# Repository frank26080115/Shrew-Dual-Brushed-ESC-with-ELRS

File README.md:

# Shrew: Dual Brushed ESC with ELRS

Shrew is family of ESCs (Electronic Speed Controller) that can drive two brushed motors, with an ELRS receiver integrated. It is designed to be as small as possible yet still pack plenty of power. It is meant for insect class combat robots.

There are three variations of Shrew

 * Shrew-Pro, for dual brushed motors up to 21A
 * Shrew-Lite, for dual brushed motors up to 3.7A
 * Shrew-Zero, not a ESC, just a receiver

All of these function as ELRS receivers with 4 or more GPIO pins, capable of controlling other ESCs or servos. These pins can output PWM, as well as better protocols such as Dshot. If you have the skills, you can even use them for I2C and such.

The input voltage ratings of Shrew is incredibly high, even Shrew-Lite can handle up to 36V, that means connecting directly to a 8S battery is not a problem (please see individual detailed specifications).

If you are using AM32 brushless ESCs with Shrew, Shrew features a webpage interface to configure the AM32 ESC. If you have 4 ESCs connected to Shrew, you can change settings on each one individually and test it immediately, all without disconnecting any wires. Plus, you can test the ESCs immediately after making a settings change through the same webpage interface.

## Design Ethos

Safety and reliability is on the top of my priority list

 * Digital protocols are safer than PWM ([why this is better](docs/Digital-Protocols-for-ESC-Control.md))
 * No-pulse failsafe mode by default ([why this is better](docs/No-Pulse-Failsafe-Mode.md))
 * No entering any unexpected modes, there is no way to accidentally enter some sort of calibration mode or binding mode
 * No dead-zone implemented, so there's no control lag at all, and there is also no need for calibration
 * Binding is done with a binding-phrase, extremely good for spare parts management of a competitive robot
 * Power input solder points are intentionally placed farther apart to prevent accidental short circuiting
 * RGB LED on it is indicative of control inputs, not just connection state
 * Top quality TCXO and a ceramic antenna for a balance between high RF performance and durability.

## User Manuals

 * [Shrew-Pro User Manual](Shrew-Pro-User-Manual.md)
 * [Shrew-Lite User Manual](Shrew-Lite-User-Manual.md)
 * [Shrew-Zero User Manual](Shrew-Zero-User-Manual.md)

## Open Source Notes

All of the circuitry is designed using CadSoft EAGLE v7. This is NOT Autodesk EAGLE, but Autodesk EAGLE can open the files.

All the manufacturing data is tailored for JLCPCB's PCBA service.

The firmware in this repo are in binary form only, but the source code for them are on a branch of a fork of ExpressLRS: https://github.com/frank26080115/ExpressLRS/tree/shrew

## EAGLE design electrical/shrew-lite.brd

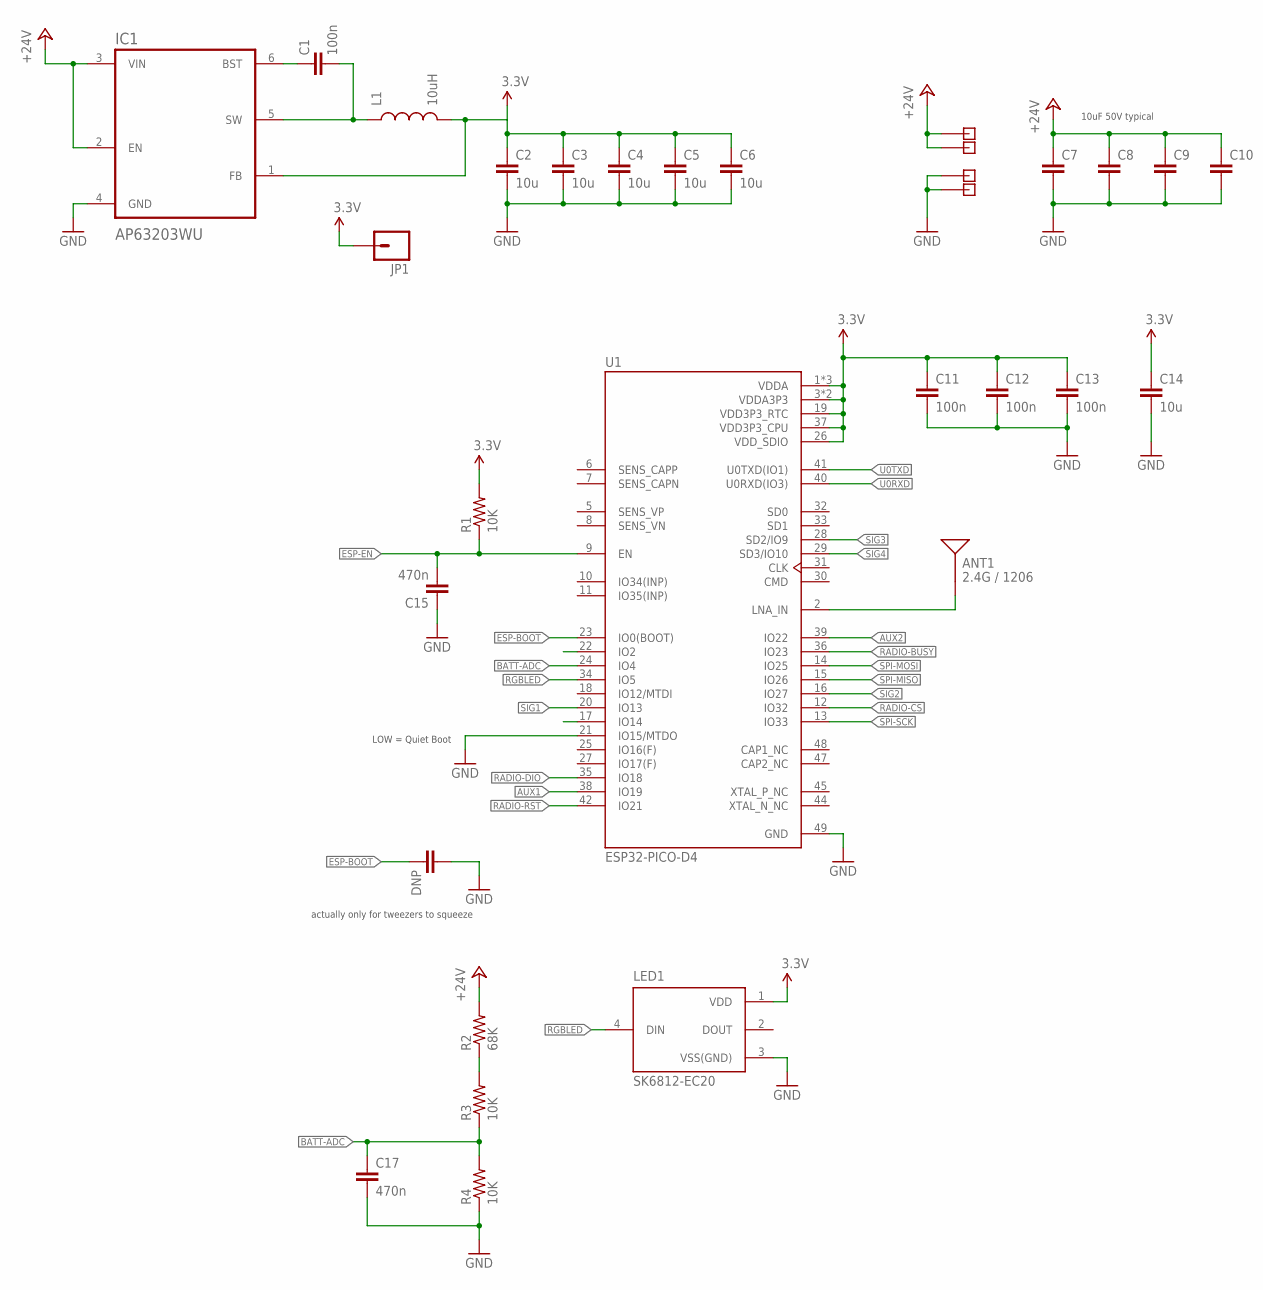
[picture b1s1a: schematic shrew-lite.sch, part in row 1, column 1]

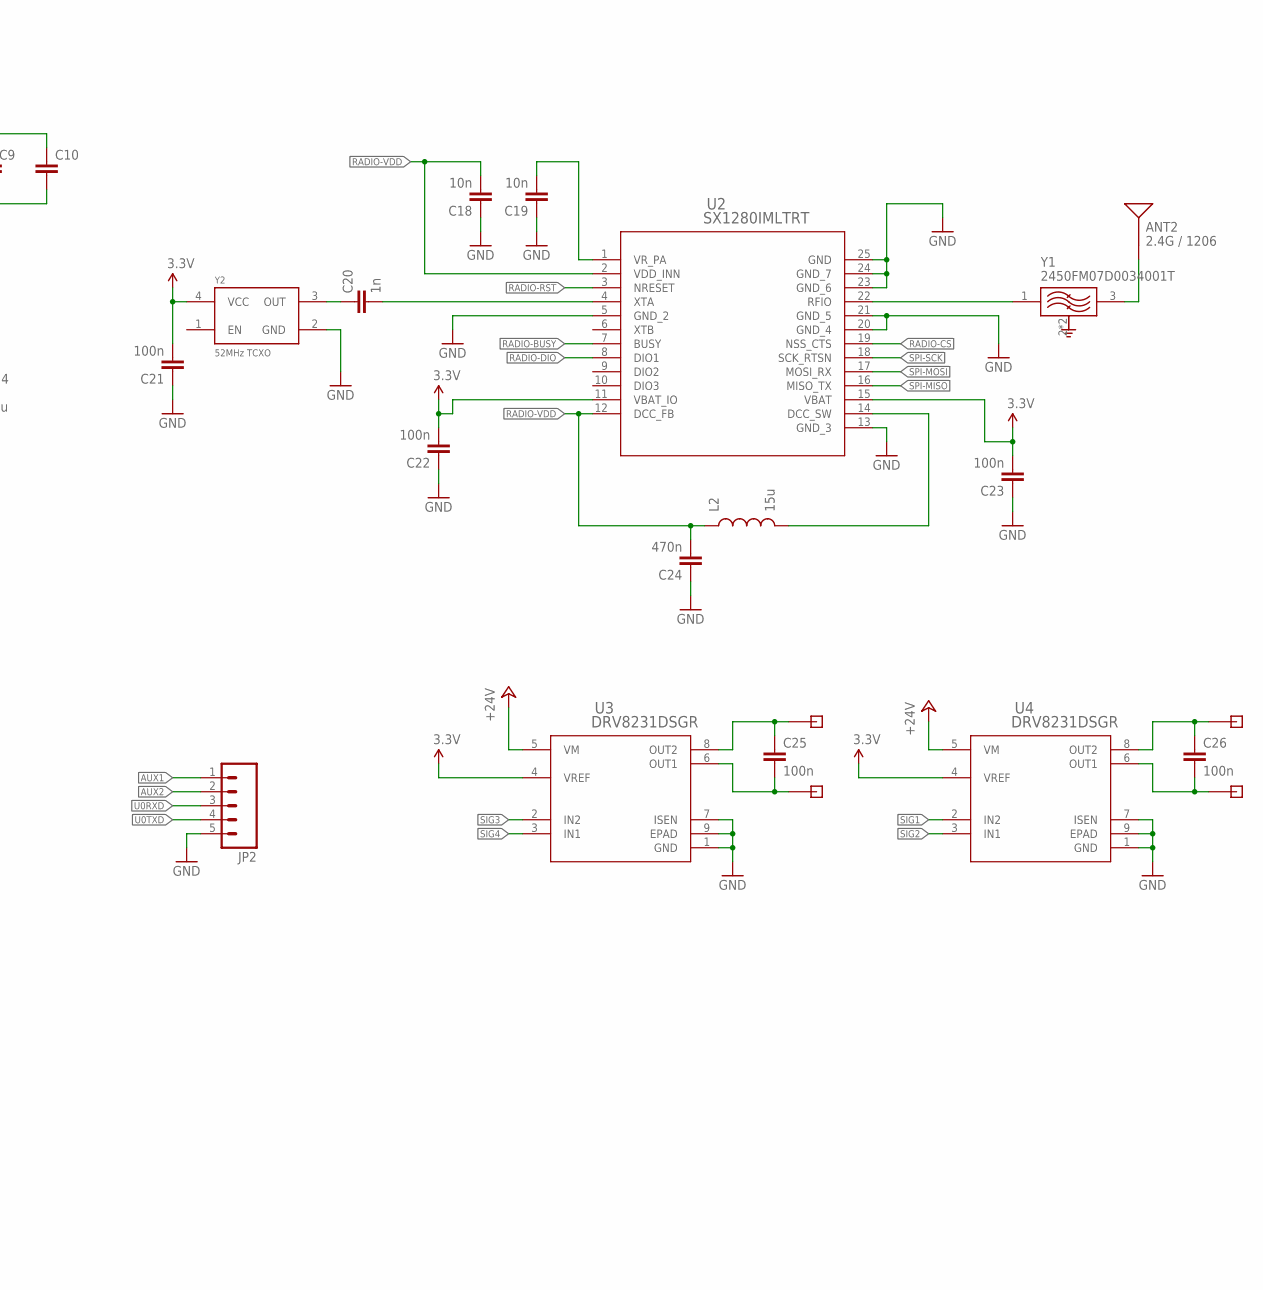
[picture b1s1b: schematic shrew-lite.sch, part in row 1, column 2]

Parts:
ANT1: 2.4G / 1206; ANTENNA-CHIP2; JLC_ROTATION 180
ANT2: 2.4G / 1206; ANTENNA-CHIP2; LCSC C127620
C1, C11, C12, C13, C21, C22, C23: 100n; 0402-REV; LCSC C1581
C2, C3, C4, C5, C6, C14: 10u; 0402-REV; LCSC C15525
C7, C8, C9, C10: 10u; 0805
C15: 470n; 0402-REV; LCSC C7393859
C16: DNP; 0402-CAP
C17, C24: 470n; 0402-REV
C18, C19: 10n; 0402-REV; LCSC C15195
C20: 1n; 0402-REV; LCSC C1523
C25, C26: 100n; 0402-CAP; LCSC C1581
IC1: AP63203WU; SOT95P280X110-6N; JLC_ROTATION 180
JP1: M01-1.0MM-TP; 1X01-1.0MM-TP
JP2: M05PTH; 1X05
L1: 10uH; 0805
L2: 15u; 0805; LCSC C6364731
LED1: SK6812-EC20
R1, R3, R4: 10K; 0402-REV; LCSC C25744
R2: 68K; 0402-REV; LCSC C2909379
U1: ESP32-PICO-D4; PQFN50P700X700X104-49N; JLC_ROTATION -90
U2: SX1280IMLTRT; QFN24_4X4_SEM; JLC_ROTATION -90
U3, U4: DRV8231DSGR; WSON8_DRV8231_TEX; JLC_ROTATION 90
X1, X2, X3, X4: PIN-1X-MED; PAD-1X-MED
X5, X6, X7, X8: PIN-1X-BIG; PAD-1X-BIG
Y1: 2450FM07D0034001T; FIL_2450FM07D0034T; LCSC C6054595
Y2: 52MHz TCXO; OSC_TG2016SMN_50.0000M-ECGNNMB; JLC_ROTATION -90

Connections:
3.3V: C2.1, C3.1, C4.1, C5.1, C6.1, C11.1, C12.1, C13.1, C14.1, C21.2, C22.2, C23.2, IC1.1 (FB), JP1.1, L1.2, LED1.1 (VDD), R1.2, U1.1 (VDDA), U1.3 (VDDA3P3), U1.4 (VDDA3P3), U1.19 (VDD3P3_RTC), U1.26 (VDD_SDIO), U1.37 (VDD3P3_CPU), U1.43 (VDDA), U1.46 (VDDA), U2.11 (VBAT_IO), U2.15 (VBAT), U3.4 (VREF), U4.4 (VREF), Y2.4 (VCC)
+24V: C7.1, C8.1, C9.1, C10.1, IC1.2 (EN), IC1.3 (VIN), R2.2, U3.5 (VM), U4.5 (VM), X1.1, X2.1
AUX1: JP2.1, U1.38 (IO19)
AUX2: JP2.2, U1.39 (IO22)
BATT-ADC: C17.1, R3.1, R4.2, U1.24 (IO4)
ESP-BOOT: C16.2, U1.23 (IO0(BOOT))
ESP-EN: C15.2, R1.1, U1.9 (EN)
GND: C2.2, C3.2, C4.2, C5.2, C6.2, C7.2, C8.2, C9.2, C10.2, C11.2, C12.2, C13.2, C14.2, C15.1, C16.1, C17.2, C18.1, C19.1, C21.1, C22.1, C23.1, C24.1, IC1.4 (GND), JP2.5, LED1.3 (VSS(GND)), R4.1, U1.21 (IO15/MTDO), U1.49 (GND), U2.5 (GND_2), U2.13 (GND_3), U2.20 (GND_4), U2.21 (GND_5), U2.23 (GND_6), U2.24 (GND_7), U2.25 (GND), U3.1 (GND), U3.7 (ISEN), U3.9 (EPAD), U4.1 (GND), U4.7 (ISEN), U4.9 (EPAD), X3.1, X4.1, Y1.2 (GND), Y1.4 (GND), Y2.2 (GND)
MOTOR1: C26.2, U4.6 (OUT1), X8.1
MOTOR2: C26.1, U4.8 (OUT2), X6.1
MOTOR3: C25.2, U3.6 (OUT1), X7.1
MOTOR4: C25.1, U3.8 (OUT2), X5.1
unnamed: ANT1.FEED, U1.2 (LNA_IN)
unnamed: C20.1, Y2.3 (OUT)
unnamed: C20.2, U2.4 (XTA)
unnamed: R2.1, R3.2
unnamed: U2.22 (RFIO), Y1.1 (IN)
unnamed: ANT2.FEED, Y1.3 (OUT)
unnamed: L2.2, U2.14 (DCC_SW)
unnamed: C1.2, IC1.5 (SW), L1.1
unnamed: C19.2, U2.1 (VR_PA)
unnamed: C1.1, IC1.6 (BST)
RADIO-BUSY: U1.36 (IO23), U2.7 (BUSY)
RADIO-CS: U1.12 (IO32), U2.19 (NSS_CTS)
RADIO-DIO: U1.35 (IO18), U2.8 (DIO1)
RADIO-RST: U1.42 (IO21), U2.3 (NRESET)
RADIO-VDD: C18.2, C24.2, L2.1, U2.2 (VDD_INN), U2.12 (DCC_FB)
RGBLED: LED1.4 (DIN), U1.34 (IO5)
SIG1: U1.20 (IO13), U4.2 (IN2)
SIG2: U1.16 (IO27), U4.3 (IN1)
SIG3: U1.28 (SD2/IO9), U3.2 (IN2)
SIG4: U1.29 (SD3/IO10), U3.3 (IN1)
SPI-MISO: U1.15 (IO26), U2.16 (MISO_TX)
SPI-MOSI: U1.14 (IO25), U2.17 (MOSI_RX)
SPI-SCK: U1.13 (IO33), U2.18 (SCK_RTSN)
U0RXD: JP2.3, U1.40 (U0RXD(IO3))
U0TXD: JP2.4, U1.41 (U0TXD(IO1))

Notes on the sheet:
actually only for tweezers to squeeze
LOW = Quiet Boot
10uF 50V typical

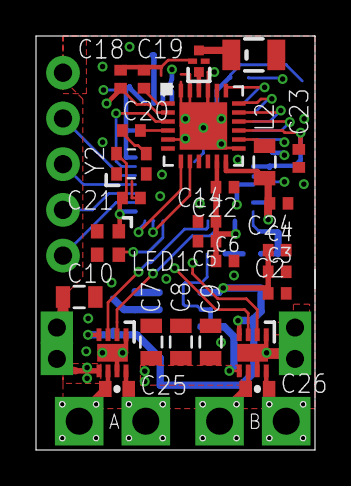
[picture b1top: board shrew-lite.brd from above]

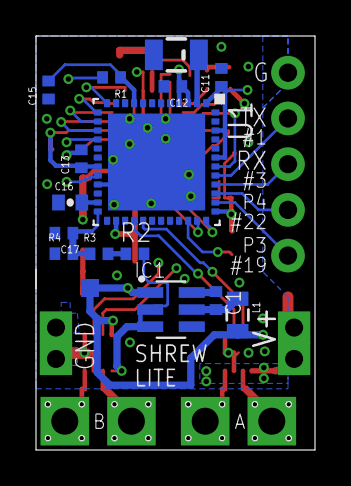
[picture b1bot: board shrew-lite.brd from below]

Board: 4 copper layers, 15.5 x 23.0 mm, 52 parts (16 on the bottom side), 37 nets.

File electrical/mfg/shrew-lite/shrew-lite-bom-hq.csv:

Comment,Designator,Footprint,LCSC Part #
0.5pF,C30,0402-REV,C258483
1n,C20,0402-REV,C307441
10K,R1 R3 R4,0402-REV,
10n,C18 C19,0402-REV,C3855387
10u,C2 C3 C4 C5 C6 C14,0402-REV,C15525
10u,C7 C8 C9 C10,0805,C2932476
10uH,L1,0805,C139245
15u,L2,0805,C486333
52MHz TCXO,Y2,OSC_TG2016SMN_50.0000M-ECGNNMB,C7503930
68K,R2,0402-REV,
100n,C1 C11 C12 C13 C21 C22 C23 C27 C28 C29 C25 C26,0402-REV,C527001
470n,C15 C17 C24,0402-REV,C106250
2450FM07D0034T,Y1,FIL_2450FM07D0034T,C2651081
ANT3216LL00R2400A,ANT1 ANT2,ANTENNA-CHIP2,C293767
AP63203WU,IC1,SOT95P280X110-6N,C780769
DRV8231DSGR,U3 U4,WSON8_DRV8231_TEX,C5139865
ESP32-PICO-D4,U1,PQFN50P700X700X104-49N,C193707
SK6812-EC20,LED1,SK6812-EC20,C2909058
SX1280IMLTRT,U2,QFN24_4X4_SEM,C125969

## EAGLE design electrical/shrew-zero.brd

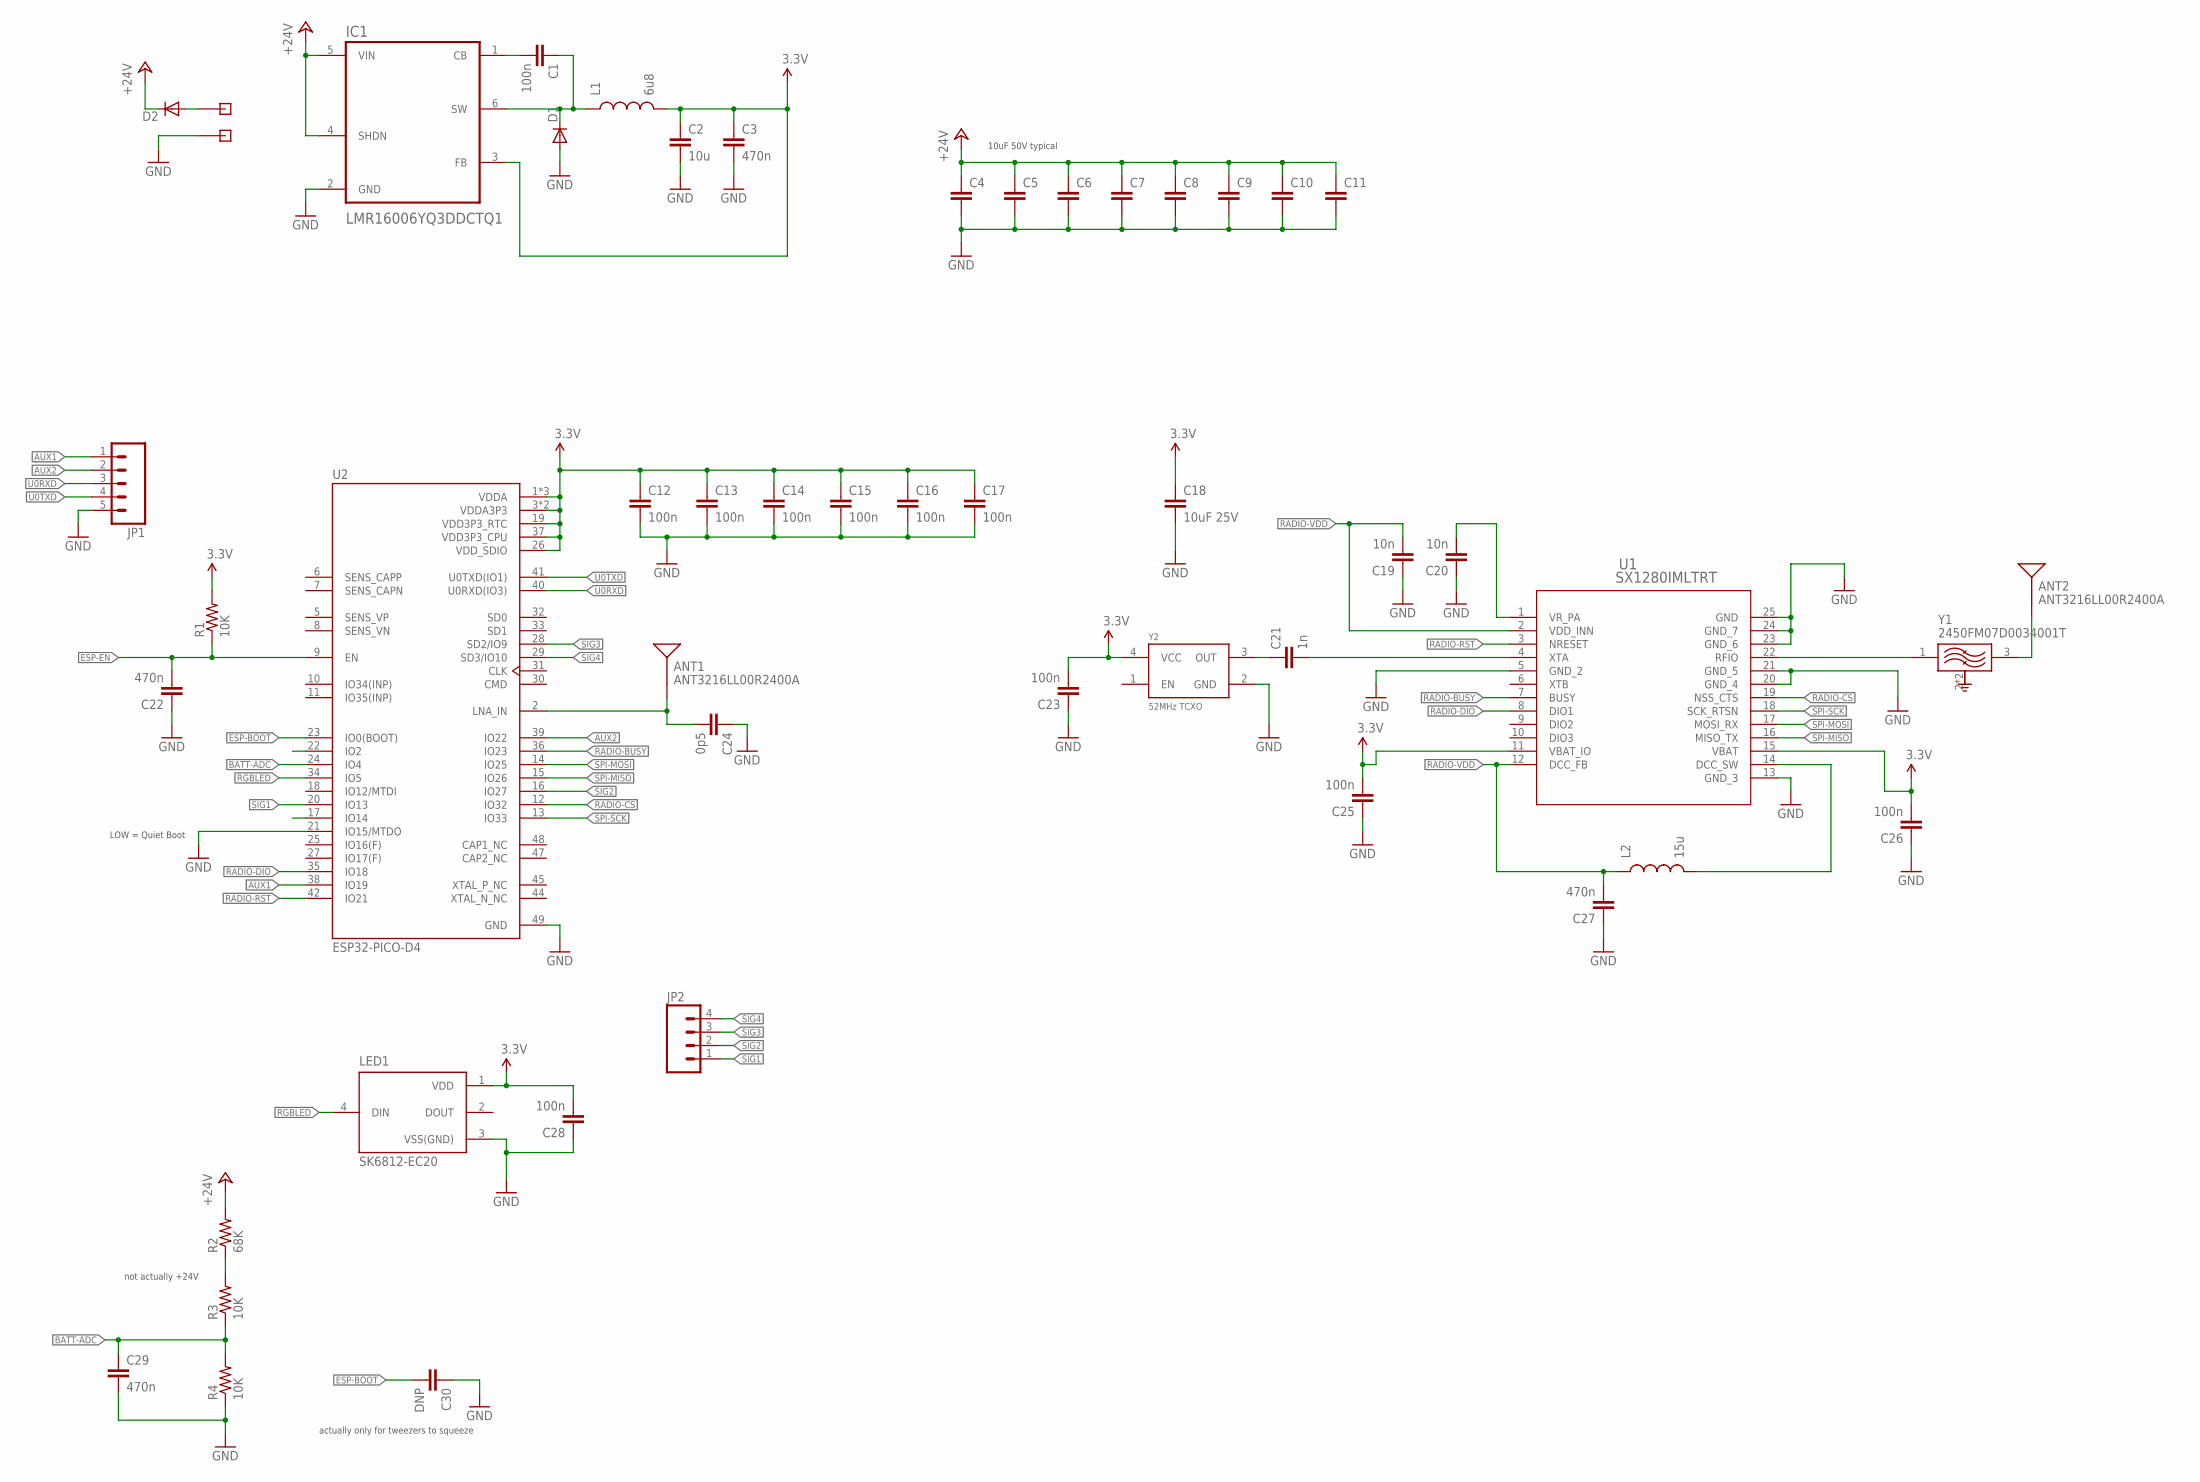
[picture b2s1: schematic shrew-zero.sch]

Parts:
ANT1, ANT2: ANT3216LL00R2400A; ANTENNA-CHIP2
C1, C12, C13, C14, C15, C16, C17, C23, C25, C26, C28: 100n; 0402-REV
C2, C4, C5, C6, C7, C8, C9, C10, C11: 10u; 0805
C3, C22, C27, C29: 470n; 0402-REV
C18: 10uF 25V; 0805
C19, C20: 10n; 0402-REV
C21: 1n; 0402-REV
C24: 0p5; 0402-REV
C30: DNP; 0402-CAP
D1: DIODESOD; SOD-323
D2: C406049; SOD-323
IC1: LMR16006YQ3DDCTQ1; SOT95P280X110-6N
JP1: M05PTH; 1X05
JP2: M04-CLEAN; 1X04-CLEAN
L1: 6u8; 0805
L2: 15u; 0805
LED1: SK6812-EC20
R1, R3, R4: 10K; 0402-REV
R2: 68K; 0402-REV
U1: SX1280IMLTRT; QFN24_4X4_SEM
U2: ESP32-PICO-D4; PQFN50P700X700X104-49N
X1, X2: PIN-1X-BIG; PAD-1X-BIG
Y1: 2450FM07D0034001T; FIL_2450FM07D0034T
Y2: 52MHz TCXO; OSC_TG2016SMN_50.0000M-ECGNNMB

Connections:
3.3V: C2.1, C3.1, C12.1, C13.1, C14.1, C15.1, C16.1, C17.1, C18.1, C23.2, C25.2, C26.2, C28.2, IC1.3 (FB), L1.2, LED1.1 (VDD), R1.2, U1.11 (VBAT_IO), U1.15 (VBAT), U2.1 (VDDA), U2.3 (VDDA3P3), U2.4 (VDDA3P3), U2.19 (VDD3P3_RTC), U2.26 (VDD_SDIO), U2.37 (VDD3P3_CPU), U2.43 (VDDA), U2.46 (VDDA), Y2.4 (VCC)
+24V: C4.1, C5.1, C6.1, C7.1, C8.1, C9.1, C10.1, C11.1, D2.1 (C), IC1.4 (SHDN), IC1.5 (VIN), R2.2
AUX1: JP1.1, U2.38 (IO19)
AUX2: JP1.2, U2.39 (IO22)
BATT-ADC: C29.1, R3.1, R4.2, U2.24 (IO4)
ESP-BOOT: C30.2, U2.23 (IO0(BOOT))
ESP-EN: C22.2, R1.1, U2.9 (EN)
GND: C2.2, C3.2, C4.2, C5.2, C6.2, C7.2, C8.2, C9.2, C10.2, C11.2, C12.2, C13.2, C14.2, C15.2, C16.2, C17.2, C18.2, C19.1, C20.1, C22.1, C23.1, C24.1, C25.1, C26.1, C27.1, C28.1, C29.2, C30.1, D1.2 (A), IC1.2 (GND), JP1.5, LED1.3 (VSS(GND)), R4.1, U1.5 (GND_2), U1.13 (GND_3), U1.20 (GND_4), U1.21 (GND_5), U1.23 (GND_6), U1.24 (GND_7), U1.25 (GND), U2.21 (IO15/MTDO), U2.49 (GND), X2.1, Y1.2 (GND), Y1.4 (GND), Y2.2 (GND)
unnamed: ANT1.FEED, C24.2, U2.2 (LNA_IN)
unnamed: C21.1, Y2.3 (OUT)
unnamed: C21.2, U1.4 (XTA)
unnamed: C1.2, IC1.1 (CB)
unnamed: U1.22 (RFIO), Y1.1 (IN)
unnamed: ANT2.FEED, Y1.3 (OUT)
unnamed: L2.2, U1.14 (DCC_SW)
unnamed: C1.1, D1.1 (C), IC1.6 (SW), L1.1
unnamed: C20.2, U1.1 (VR_PA)
unnamed: D2.2 (A), X1.1
RADIO-BUSY: U1.7 (BUSY), U2.36 (IO23)
RADIO-CS: U1.19 (NSS_CTS), U2.12 (IO32)
RADIO-DIO: U1.8 (DIO1), U2.35 (IO18)
RADIO-RST: U1.3 (NRESET), U2.42 (IO21)
RADIO-VDD: C19.2, C27.2, L2.1, U1.2 (VDD_INN), U1.12 (DCC_FB)
RGBLED: LED1.4 (DIN), U2.34 (IO5)
SIG1: JP2.1, U2.20 (IO13)
SIG2: JP2.2, U2.16 (IO27)
SIG3: JP2.3, U2.28 (SD2/IO9)
SIG4: JP2.4, U2.29 (SD3/IO10)
SPI-MISO: U1.16 (MISO_TX), U2.15 (IO26)
SPI-MOSI: U1.17 (MOSI_RX), U2.14 (IO25)
SPI-SCK: U1.18 (SCK_RTSN), U2.13 (IO33)
U0RXD: JP1.3, U2.40 (U0RXD(IO3))
U0TXD: JP1.4, U2.41 (U0TXD(IO1))
V-ADC: R2.1, R3.2

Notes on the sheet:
actually only for tweezers to squeeze
not actually +24V
LOW = Quiet Boot
10uF 50V typical

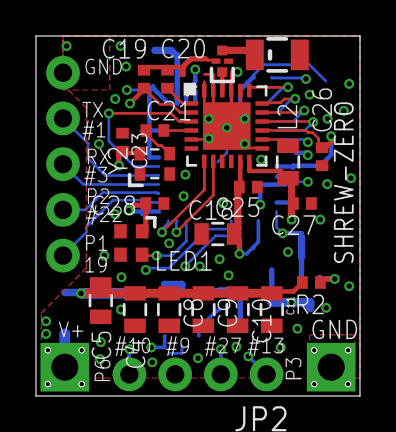
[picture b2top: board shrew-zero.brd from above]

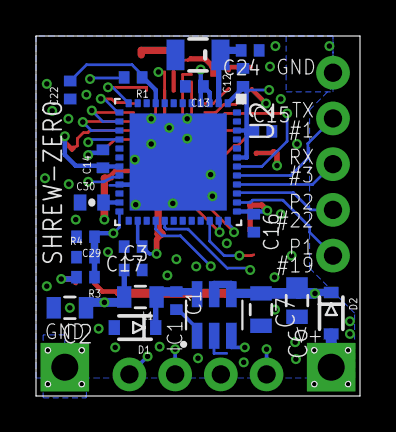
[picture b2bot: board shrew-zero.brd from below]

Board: 4 copper layers, 18.0 x 20.0 mm, 50 parts (24 on the bottom side), 34 nets.

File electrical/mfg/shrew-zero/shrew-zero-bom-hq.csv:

Comment,Designator,Footprint,LCSC Part #
schottky 40V,D1,SOD-323,C151511
60V 1A,D2,SOD-323,C406049
0p5,C24,0402-REV,C258483
1n,C21,0402-REV,C307441
10uH,L1,0805,C139245
10K,R1 R3 R4,0402-REV,
10n,C19 C20,0402-REV,C3855387
10u,C2 C4 C5 C6 C7 C8 C9 C10 C11 C18,0805,C2932476
15u,L2,0805,C486333
52MHz TCXO,Y2,OSC_TG2016SMN_50.0000M-ECGNNMB,C7503930
68K,R2,0402-REV,
100n,C1 C12 C13 C14 C15 C16 C17 C23 C25 C26 C28,0402-REV,C527001
470n,C3 C22 C27 C29,0402-REV,C106250
2450FM07D0034001T,Y1,FIL_2450FM07D0034T,C2651081
ANT3216LL00R2400A,ANT1 ANT2,ANTENNA-CHIP2,C293767
ESP32-PICO-D4,U2,PQFN50P700X700X104-49N,C193707
LMR16006YQ3DDCTQ1,IC1,SOT95P280X110-6N,C2071392
SK6812-EC20,LED1,SK6812-EC20,C2909058
SX1280IMLTRT,U1,QFN24_4X4_SEM,C125969

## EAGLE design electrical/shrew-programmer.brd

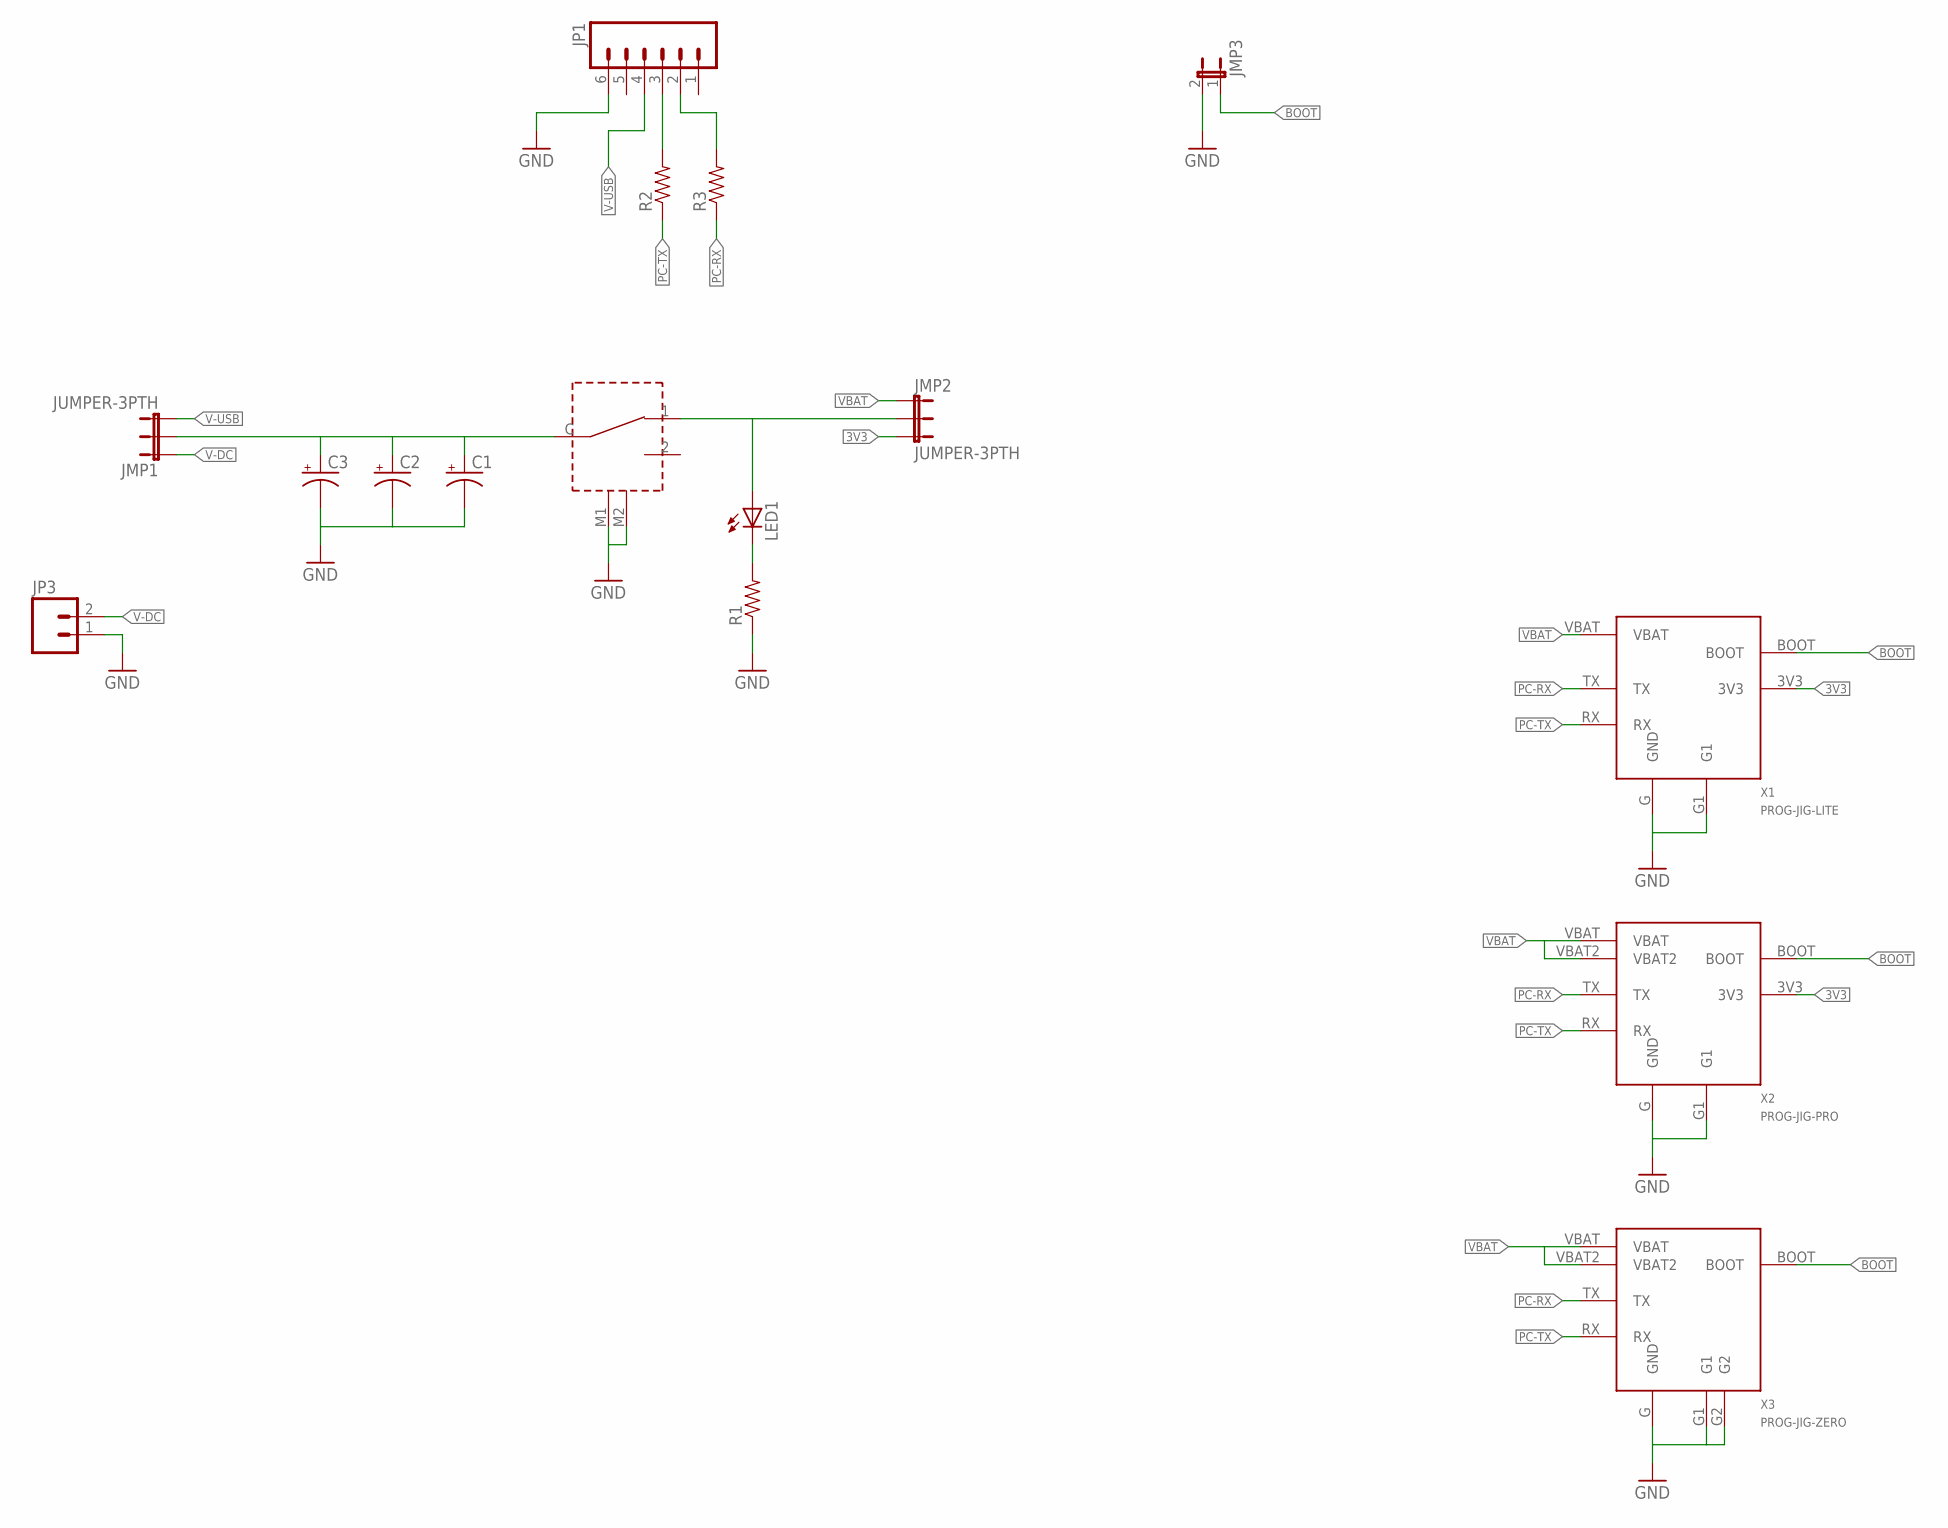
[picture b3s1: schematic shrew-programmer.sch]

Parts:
C1, C2, C3: CAP_POLPTH1; CPOL-RADIAL-100UF-25V
JMP1, JMP2: JUMPER-3PTH; 1X03
JMP3: JUMPER-2PTH; 1X02
JP1: M06LONGPADS; 1X06_LONGPADS
JP3: M023.5MM; SCREWTERMINAL-3.5MM-2
LED1: LED1206; LED-1206
R1, R2, R3: RESISTOR0603-RES; 0603-RES
SW1: SWITCH-ROCKER-3PIN-2MNT
X1: PROG-JIG-LITE
X2: PROG-JIG-PRO
X3: PROG-JIG-ZERO

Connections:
3V3: JMP2.3, X1.3V3, X2.3V3
BOOT: JMP3.1, X1.BOOT, X2.BOOT, X3.BOOT
GND: C1.2 (-), C2.2 (-), C3.2 (-), JMP3.2, JP1.6, JP3.1, R1.1, SW1.M1, SW1.M2, X1.G (GND), X1.G1, X2.G (GND), X2.G1, X3.G (GND), X3.G1, X3.G2
unnamed: JP1.3, R2.2
unnamed: JP1.2, R3.2
unnamed: C1.1 (+), C2.1 (+), C3.1 (+), JMP1.2, SW1.C
unnamed: LED1.C, R1.2
unnamed: JMP2.2, LED1.A, SW1.1
PC-RX: R3.1, X1.TX, X2.TX, X3.TX
PC-TX: R2.1, X1.RX, X2.RX, X3.RX
V-DC: JMP1.1, JP3.2
V-USB: JMP1.3, JP1.4
VBAT: JMP2.1, X1.VBAT, X2.VBAT, X2.VBAT2, X3.VBAT, X3.VBAT2

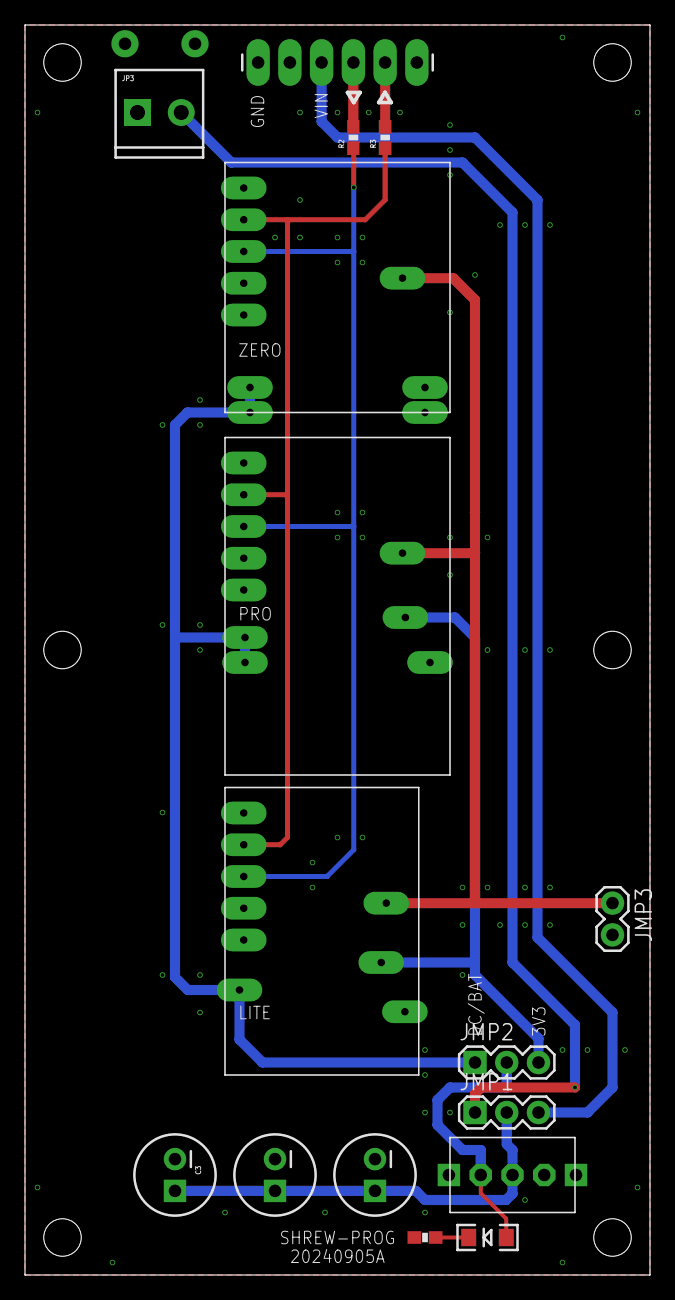
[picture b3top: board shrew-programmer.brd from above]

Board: 2 copper layers, 50.0 x 100.0 mm, 16 parts (0 on the bottom side), 13 nets.

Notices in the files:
parts and their libraries:
COPYRIGHT: Copyright (C) 2024 Ultra Librarian. All rights reserved.
